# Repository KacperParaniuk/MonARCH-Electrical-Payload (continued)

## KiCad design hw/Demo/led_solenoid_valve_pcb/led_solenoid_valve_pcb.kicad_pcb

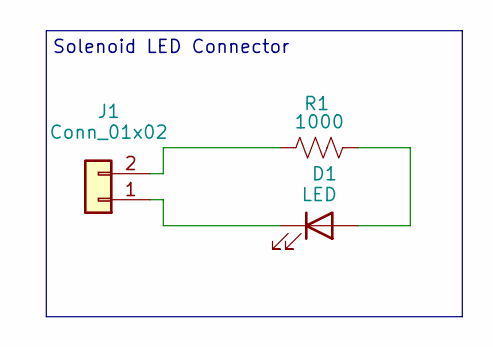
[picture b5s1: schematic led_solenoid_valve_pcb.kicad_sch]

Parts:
D1: LED; LED_0603_1608Metric
J1: Conn_01x02; PinHeader_1x02_P2.54mm_Vertical
R1: 1000; R_0603_1608Metric_Pad0.98x0.95mm_HandSolder

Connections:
unnamed: D1.2 (A), R1.2
unnamed: D1.1 (K), J1.1
unnamed: J1.2, R1.1

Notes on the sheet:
Solenoid LED Connector

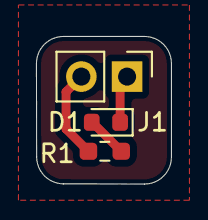
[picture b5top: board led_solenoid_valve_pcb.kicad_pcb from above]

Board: 2 copper layers, 7.5 x 8.2 mm, 3 parts (0 on the bottom side), 3 nets.

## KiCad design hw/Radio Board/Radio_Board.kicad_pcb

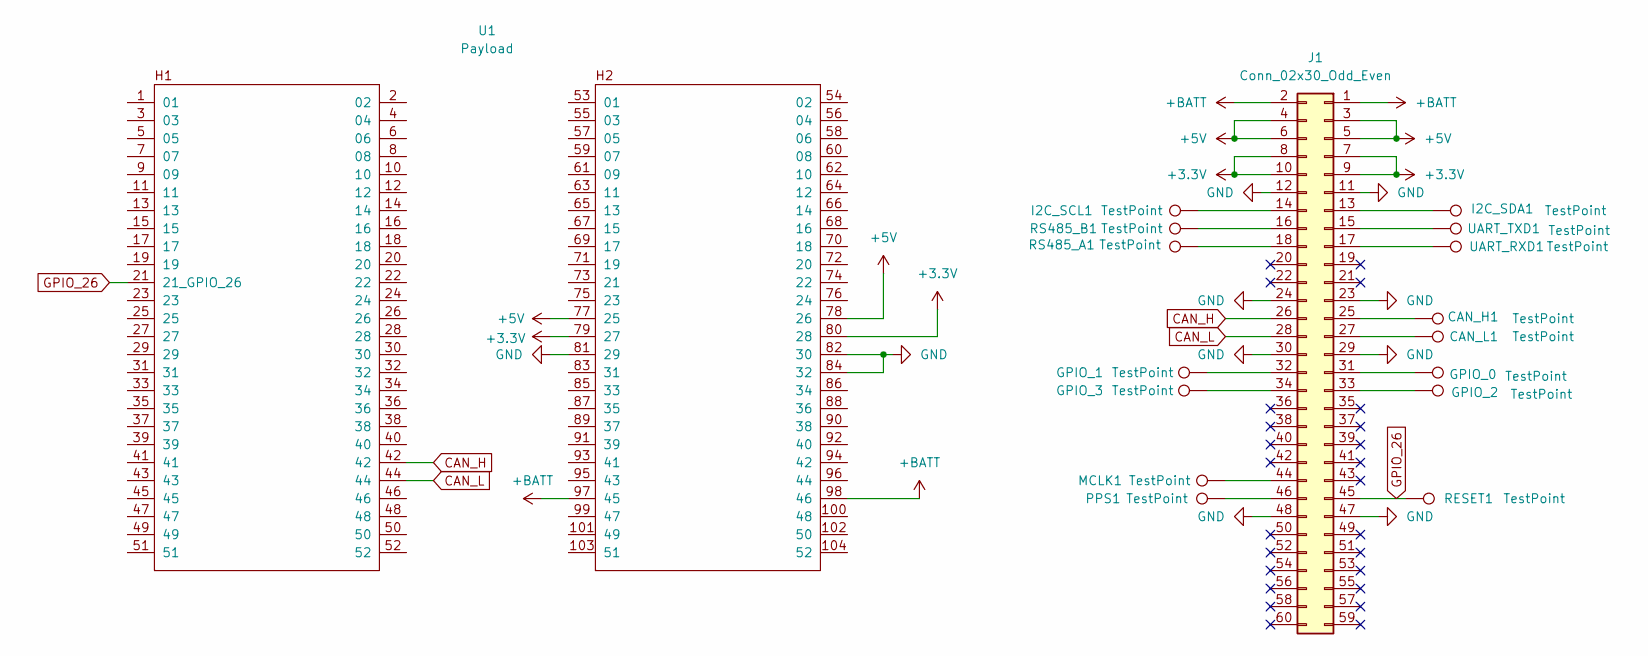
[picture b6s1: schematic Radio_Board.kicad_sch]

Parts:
CAN_H1: TestPoint; TestPoint_Keystone_5000-5004_Miniature
CAN_L1: TestPoint; TestPoint_Keystone_5000-5004_Miniature
GPIO_0, GPIO_1, GPIO_2, GPIO_3: TestPoint; TestPoint_Keystone_5000-5004_Miniature
I2C_SCL1, I2C_SDA1: TestPoint; TestPoint_Keystone_5000-5004_Miniature
J1: Conn_02x30_Odd_Even; CON_543630689
MCLK1: TestPoint; TestPoint_Keystone_5000-5004_Miniature
PPS1: TestPoint; TestPoint_Keystone_5000-5004_Miniature
RESET1: TestPoint; TestPoint_Keystone_5000-5004_Miniature
RS485_A1, RS485_B1: TestPoint; TestPoint_Keystone_5000-5004_Miniature
U1: Payload; PC104-Standard
UART_RXD1: TestPoint; TestPoint_Keystone_5000-5004_Miniature
UART_TXD1: TestPoint; TestPoint_Keystone_5000-5004_Miniature

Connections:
+3.3V: J1.7, J1.8, J1.9, J1.10, U1.79 (27), U1.80 (28)
+5V: J1.3, J1.4, J1.5, J1.6, U1.77 (25), U1.78 (26)
+BATT: J1.1, J1.2, U1.97 (45), U1.98 (46)
CAN_H: J1.26, U1.42
CAN_L: J1.28, U1.44
GND: J1.11, J1.12, J1.23, J1.24, J1.29, J1.30, J1.47, J1.48, U1.81 (29), U1.82 (30), U1.84 (32)
GPIO_26: J1.45, RESET1.1, U1.21 (21_GPIO_26)
unnamed: I2C_SDA1.1, J1.13
unnamed: I2C_SCL1.1, J1.14
unnamed: J1.15, UART_TXD1.1
unnamed: J1.16, RS485_B1.1
unnamed: J1.17, UART_RXD1.1
unnamed: J1.18, RS485_A1.1
unnamed: CAN_H1.1, J1.25
unnamed: CAN_L1.1, J1.27
unnamed: GPIO_0.1, J1.31
unnamed: GPIO_1.1, J1.32
unnamed: GPIO_2.1, J1.33
unnamed: GPIO_3.1, J1.34
unnamed: J1.44, MCLK1.1
unnamed: J1.46, PPS1.1

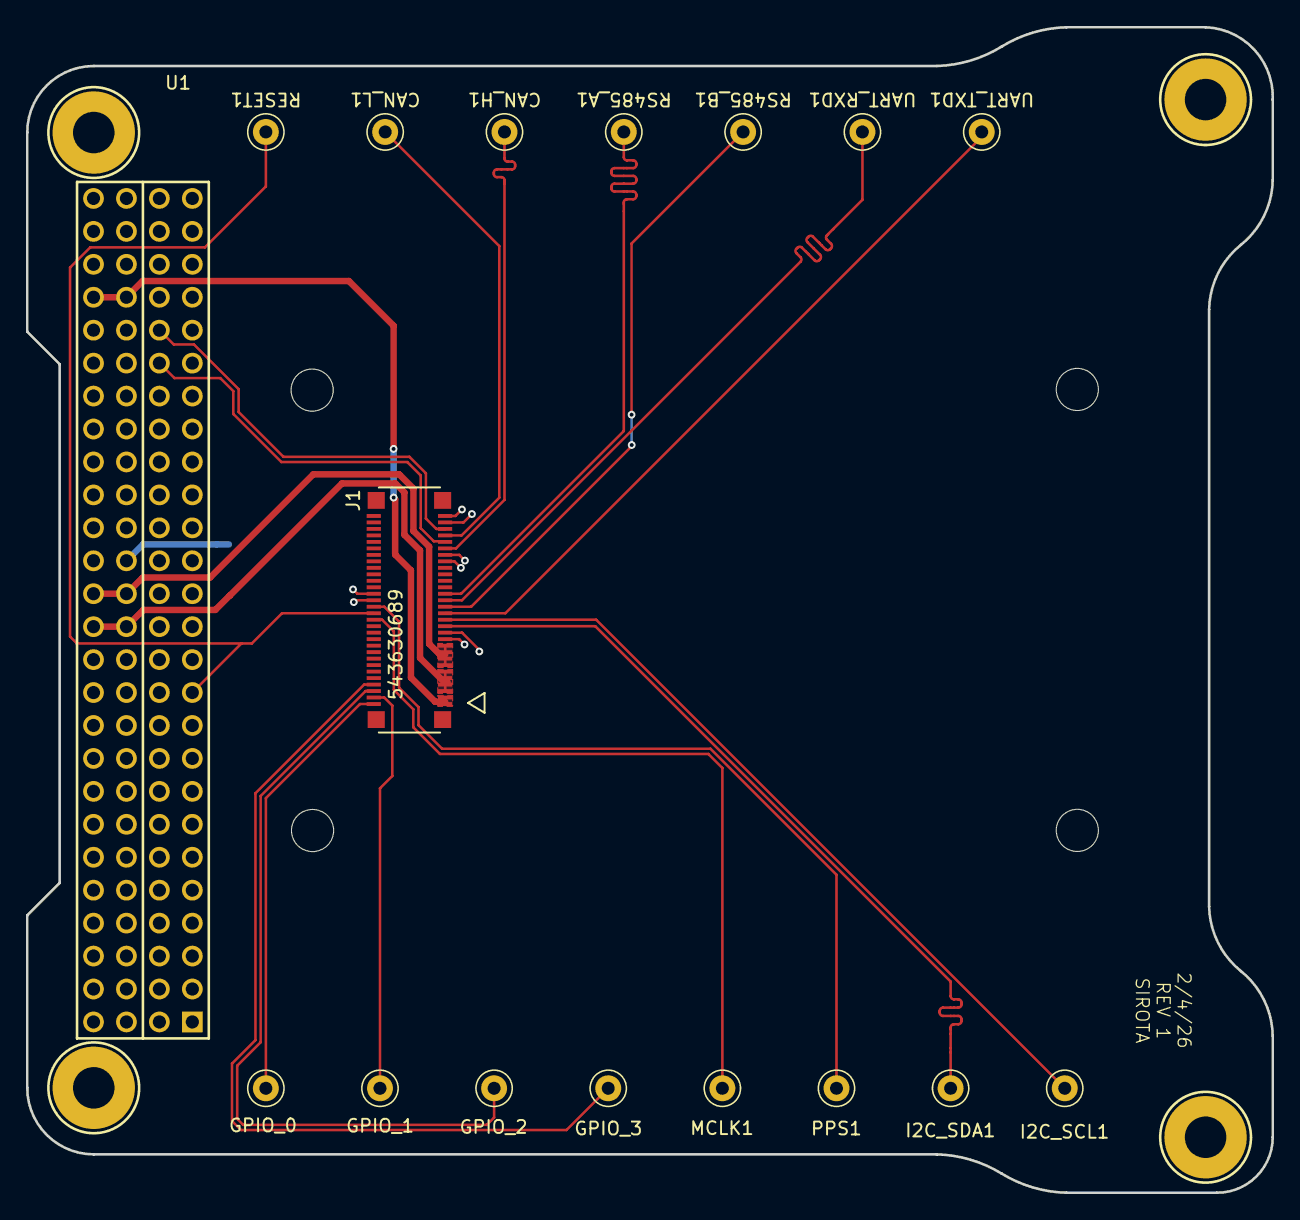
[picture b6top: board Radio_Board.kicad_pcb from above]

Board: 2 copper layers, 96.0 x 89.9 mm, 17 parts (0 on the bottom side), 21 nets.

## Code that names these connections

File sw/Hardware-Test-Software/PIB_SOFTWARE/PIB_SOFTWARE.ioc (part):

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Mcu.Name=STM32L4A6VGTx
Mcu.Package=LQFP100
Mcu.UserName=STM32L4A6VGTx
PA0.GPIOParameters=GPIO_Label
PA0.GPIO_Label=UART4_TX_PPU
PA0.Mode=Asynchronous
PA0.Signal=UART4_TX
PA1.GPIOParameters=GPIO_Label
PA1.GPIO_Label=UART4_RX_PPU
PA1.Mode=Asynchronous
PA1.Signal=UART4_RX
PA10.GPIOParameters=GPIO_Label
PA10.GPIO_Label=heater_en
PA10.Signal=GPIO_Output
PA11.GPIOParameters=GPIO_Label
PA11.GPIO_Label=valve18
PA11.Signal=GPIO_Output
PA13\ (JTMS/SWDIO).Mode=Trace_Asynchronous_SW
PA13\ (JTMS/SWDIO).Signal=SYS_JTMS-SWDIO
PA14\ (JTCK/SWCLK).Mode=Trace_Asynchronous_SW
PA14\ (JTCK/SWCLK).Signal=SYS_JTCK-SWCLK
PA4.GPIOParameters=GPIO_Label
PA4.GPIO_Label=ADC_EN
PA4.Signal=GPIO_Output
PA5.GPIOParameters=GPIO_Label
PA5.GPIO_Label=SPI1_SCK_BAT
PA5.Mode=Full_Duplex_Master
PA5.Signal=SPI1_SCK
PA6.GPIOParameters=GPIO_Label
PA6.GPIO_Label=SPI1_MISO_BAT
PA6.Mode=Full_Duplex_Master
PA6.Signal=SPI1_MISO
PA7.GPIOParameters=GPIO_Label
PA7.GPIO_Label=SPI1_MOSI_BAT
PA7.Mode=Full_Duplex_Master
PA7.Signal=SPI1_MOSI
PA8.GPIOParameters=GPIO_Label
PA8.GPIO_Label=valve12
PA8.Signal=GPIO_Output
PB10.GPIOParameters=GPIO_Label
PB10.GPIO_Label=I2C4_SCL_BREAKOUT
PB10.Mode=I2C
PB10.Signal=I2C4_SCL
PB11.GPIOParameters=GPIO_Label
PB11.GPIO_Label=I2C4_SDA_BREAKOUT
PB11.Mode=I2C
PB11.Signal=I2C4_SDA
PB12.GPIOParameters=GPIO_Label
PB12.GPIO_Label=valve1
PB12.Signal=GPIO_Output
PB13.GPIOParameters=GPIO_Label
PB13.GPIO_Label=valve2
PB13.Signal=GPIO_Output
PB14.GPIOParameters=GPIO_Label
PB14.GPIO_Label=valve3
PB14.Signal=GPIO_Output
PB15.GPIOParameters=GPIO_Label
PB15.GPIO_Label=valve5
PB15.Signal=GPIO_Output
PB3\ (JTDO/TRACESWO).Mode=Trace_Asynchronous_SW
PB3\ (JTDO/TRACESWO).Signal=SYS_JTDO-SWO
PB9.GPIOParameters=GPIO_Label
PB9.GPIO_Label=T1_EN
PB9.Signal=GPIO_Output
PC10.GPIOParameters=GPIO_Label
PC10.GPIO_Label=valve13
PC10.Signal=GPIO_Output
PC11.GPIOParameters=GPIO_Label
PC11.GPIO_Label=valve14
PC11.Signal=GPIO_Output
PC12.GPIOParameters=GPIO_Label
PC12.GPIO_Label=valve16
PC12.Signal=GPIO_Output
PC4.GPIOParameters=GPIO_Label
PC4.GPIO_Label=USART3_TX_OBC
PC4.Mode=Asynchronous
PC4.Signal=USART3_TX
PC5.GPIOParameters=GPIO_Label
PC5.GPIO_Label=USART3_RX_OBC
PC5.Mode=Asynchronous
PC5.Signal=USART3_RX
PC6.GPIOParameters=GPIO_Label
PC6.GPIO_Label=TIM8_CH1_VALVE4
PC6.Signal=S_TIM8_CH1
PC7.GPIOParameters=GPIO_Label
PC7.GPIO_Label=valve9
PC7.Signal=GPIO_Output
PC8.GPIOParameters=GPIO_Label
PC8.GPIO_Label=valve10
PC8.Signal=GPIO_Output
PC9.GPIOParameters=GPIO_Label
PC9.GPIO_Label=valve11
PC9.Signal=GPIO_Output
PD0.GPIOParameters=GPIO_Label
PD0.GPIO_Label=valve17
PD0.Signal=GPIO_Output
PD1.GPIOParameters=GPIO_Label
PD1.GPIO_Label=TC_SPI2_SCK
PD1.Mode=Full_Duplex_Master
PD1.Signal=SPI2_SCK
PD2.GPIOParameters=GPIO_Label
PD2.GPIO_Label=valve15
PD2.Signal=GPIO_Output
PD3.GPIOParameters=GPIO_Label
PD3.GPIO_Label=TC_SPI2_MISO
PD3.Mode=Full_Duplex_Master
PD3.Signal=SPI2_MISO
PD4.GPIOParameters=GPIO_Label
PD4.GPIO_Label=TC_SPI2_MOSI
PD4.Mode=Full_Duplex_Master
PD4.Signal=SPI2_MOSI
PD8.GPIOParameters=GPIO_Label
PD8.GPIO_Label=valve7
PD8.Signal=GPIO_Output
PD9.GPIOParameters=GPIO_Label
PD9.GPIO_Label=valve8
PD9.Signal=GPIO_Output
PE0.GPIOParameters=GPIO_Label
PE0.GPIO_Label=T3_EN
PE0.Signal=GPIO_Output
PE1.GPIOParameters=GPIO_Label
PE1.GPIO_Label=T5_EN
PE1.Signal=GPIO_Output
PE13.GPIOParameters=GPIO_Label
PE13.GPIO_Label=LED_PIN_AMBER
PE13.Signal=GPIO_Output
PE14.GPIOParameters=GPIO_Label
PE14.GPIO_Label=LED_PIN_GREEN
PE14.Signal=GPIO_Output
PE15.GPIOParameters=GPIO_Label
PE15.GPIO_Label=LED_PIN_RED
PE15.Signal=GPIO_Output
PE2.GPIOParameters=GPIO_Label
PE2.GPIO_Label=T4_EN
PE2.Signal=GPIO_Output
PE3.GPIOParameters=GPIO_Label
PE3.GPIO_Label=T2_EN
PE3.Signal=GPIO_Output
PE4.GPIOParameters=GPIO_Label
PE4.GPIO_Label=PT_EN
PE4.Signal=GPIO_Output
PE5.GPIOParameters=GPIO_Label
PE5.GPIO_Label=TIM3_CH3_VALVE6
PE5.Signal=S_TIM3_CH3
PH0-OSC_IN\ (PH0).GPIOParameters=GPIO_Label
PH0-OSC_IN\ (PH0).GPIO_Label=POW12_EN
PH0-OSC_IN\ (PH0).Signal=GPIO_Output
RCC.HSE_VALUE=8000000
RCC.SYSCLKFreq_VALUE=4000000
board=custom

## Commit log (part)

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2026-02-18 initial file
2026-02-18 placeholders
2026-02-21 First Commit- Breakout Board + Software Setup
2026-02-22 Components selection for valves so far
2026-02-23 More components
2026-02-24 Clean Up
2026-02-24 Official PIB Code + FDC2214 Driver
2026-02-24 Added FDC2214 + INA-226-Q1 to schematic
2026-02-24 Main Software Structure
2026-02-24 Pins.h + GPIO_driver.h
2026-02-24 Schematic Review
2026-02-24 PCB shenanigans
2026-02-25 Breakout Board Work
2026-02-26 FDC2214 LC Tank Work
2026-02-26 GPIO Driver + INA226-Q Driver Set Up + Initial I2C Bus Setup
2026-02-27 Schematic Work + Cleanup + Initial PCB Design
2026-02-27 PCB updates
2026-02-28 Footprints, Connectors, and Routing
2026-03-01 MOSFET Driver, Valve Configs, I2C Configs, I2C Driver
2026-03-02 PIB Layout Update 3/2
2026-03-03 40 Mhz Clock Work + Test Software for Main Control Flow on Dev Board
2026-03-04 Crystal Clock Completion, All Pins Assigned, More Routing Work
2026-03-04 Test push post move
2026-03-04 Revert "Crystal Clock Completion, All Pins Assigned, More Routing Work"
    This reverts commit 432819c756e1f3cf9abb2627b488983cb7a3cfe3
2026-03-04 remove tests file
2026-03-04 Breakout Board History Fix
2026-03-05 SOFTWARE FIX + More sensor drivers (IN PROGRESS) -> Need to work on integration with stm32l4a6
2026-03-06 Amplifier Initial Setup / Routing Work
2026-03-06 PIB Progress
    Most MCU pins selected. more to come.
2026-03-07 Deletion of Components -> Ammeter Circuit Scraped + External 40 MHz Clock + Pull Up Pins on I2C
2026-03-08 PIB layout update
    done pending Ben O approval
2026-03-08 Final Breakout Board Work
2026-03-08 Breakout Board DONE
2026-03-09 PIB minor updates & radio board
2026-03-09 radio board goodbye
2026-03-09 board review
2026-03-09 board review changes
2026-03-10 FIXES after Review
2026-03-10 WIP: local kicad changes
2026-03-10 minor tweaks
2026-03-10 FIXES V2
2026-03-10 more minor tweaks
2026-03-10 fixed vias
2026-03-11 Changes V3 -> Fixed I2C Line Lengths, Fixed Connection, and RAN DRC w/ no issues, and changed the fill to solid
2026-03-12 I2C lengths breakout board
2026-03-12 PIB Signature
2026-03-12 Silk Screen Identification
2026-03-14 Final Pin Allocation + SPI Driver + FDC2214 Driver Import (need to convert from c++ to c)
2026-03-14 UART Abstraction Driver
2026-03-15 SPI No-OS Driver Integration Build Success
2026-03-16 NO-OS Driver Deletion (Not needed) + AD7124 Driver Conversion from No-OS to HAL
2026-03-17 AD7124 Full Integration -> Init + UART Polling Loop
2026-03-18 TC's Full MAX31856 Driver Integration + TC UART Loop Integration
2026-03-19 Simple Solenoid Control Integration (ON/OFF)
2026-03-22 FDC2214 Custom Driver + Full UART Commands
2026-03-27 Printf for ST-LINK Setup and Debug Done + Test Printf integration
2026-03-28 ADC7124 PC104 Voltage/Current Readings Setup + Debug Prints + UART CMDS for PC104 V/I Readings
2026-03-29 Device ID's
2026-03-29 Heat Catalyst Function
2026-04-01 Pinouts Sheet
2026-04-04 fill accumulators test control sequence + pinout check valid + imported drivers for PID + cubemx setup timer for PWM signal control
2026-04-30 Comment out LED BLINK
2026-05-02 SWD Setup Test #1
2026-06-11 Lots of testing
2026-06-29 Software/Hardware
2026-06-29 Software Debugging Fun -> AD7124, MAX31856, FD2214
2026-06-30 BOOT PIN FIX + NRST PIN FIX
2026-06-30 New REV2 addition
2026-06-30 Debugging LEDS, Power LEDs, and Button for NRST
2026-06-30 MCU Power Pins Fix
2026-06-30 Connector Additions
2026-06-30 LED 12 VOLT Values / New Connector Footprints added
